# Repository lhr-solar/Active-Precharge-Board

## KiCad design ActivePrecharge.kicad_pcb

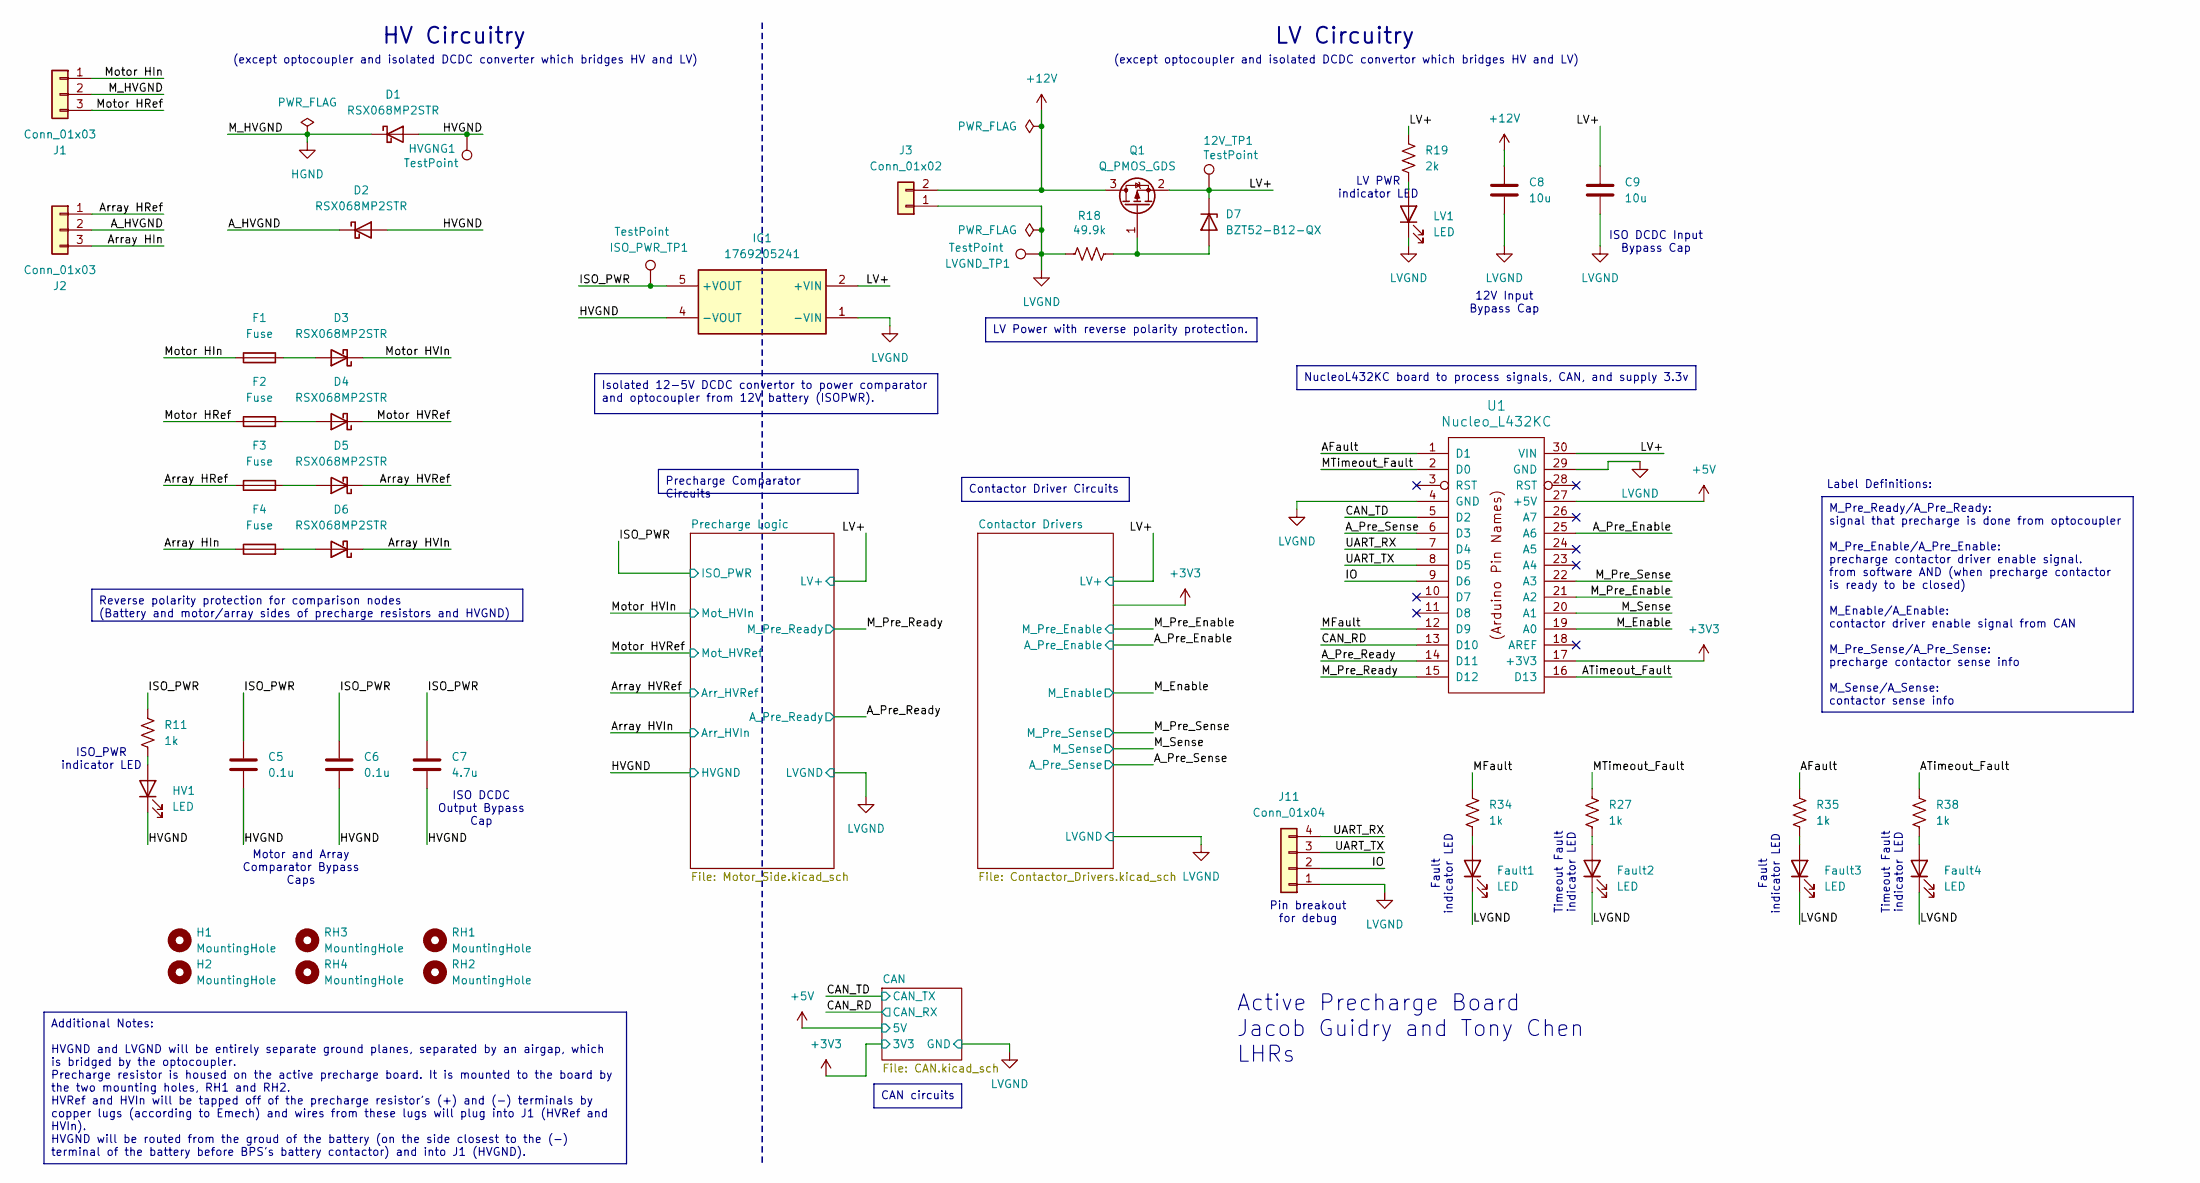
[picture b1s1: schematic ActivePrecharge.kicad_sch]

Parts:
12V_TP1: TestPoint; TestPoint_HEX_3mmID
C5, C6: 0.1u; C_0805_2012Metric
C7: 4.7u; C_0805_2012Metric
C8, C9: 10u; C_0805_2012Metric
D1, D2, D3, D4, D5, D6: RSX068MP2STR; D_SOD-123F
D7: BZT52-B12-QX; BZT52B12QX
F1, F2, F3, F4: Fuse; Fuseholder_Blade_Mini_Keystone_3568
Fault1, Fault2, Fault3, Fault4: LED; LED_0805_2012Metric
H1, H2: MountingHole; MountingHole_3mm
HV1: LED; LED_0805_2012Metric
HVGNG1: TestPoint; TestPoint_HEX_3mmID
IC1: 1769205241; Manufacturer_Part_Number 1769205241
ISO_PWR_TP1: TestPoint; TestPoint_HEX_3mmID
J1, J2: Conn_01x03; Molex_MicroFit3.0_1x3xP3.00mm_PolarizingPeg_Vertical
J3: Conn_01x02; Molex_MicroFit3.0_1x2xP3.00mm_PolarizingPeg_Vertical
J11: Conn_01x04; PinHeader_1x04_P2.54mm_Vertical
LV1: LED; LED_0805_2012Metric
LVGND_TP1: TestPoint; TestPoint_HEX_3mmID
Q1: Q_PMOS_GDS; SOT-23-3
R11, R27, R34, R35, R38: 1k; R_0805_2012Metric
R18: 49.9k; R_0805_2012Metric
R19: 2k; R_0805_2012Metric
RH1, RH2, RH3, RH4: MountingHole; MountingHole_3.2mm_M3
U1: Nucleo_L432KC; NucleoL432KC

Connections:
+3V3: U1.17 (+3V3); also elsewhere on the board
+5V: U1.27 (+5V); also elsewhere on the board
+12V: C8.1, J3.2, Q1.3 (S)
/AFault: R35.1, U1.1 (D1)
/ATimeout_Fault: R38.1, U1.16 (D13)
/A_HVGND: D2.1 (K), J2.2
/A_Pre_Enable: U1.25 (A6); also elsewhere on the board
/A_Pre_Ready: U1.14 (D11); also elsewhere on the board
/A_Pre_Sense: U1.6 (D3); also elsewhere on the board
/Array HIn: F4.1, J2.3
/Array HRef: F3.1, J2.1
/Array HVIn: D6.1 (K); also elsewhere on the board
/Array HVRef: D5.1 (K); also elsewhere on the board
/CAN_RD: U1.13 (D10); also elsewhere on the board
/CAN_TD: U1.5 (D2); also elsewhere on the board
/HVGND: C5.2, C6.2, C7.2, D1.2 (A), D2.2 (A), HV1.1 (K), HVGNG1.1, IC1.4 (-VOUT); also elsewhere on the board
/IO: J11.2, U1.9 (D6)
/ISO_PWR: C5.1, C6.1, C7.1, IC1.5 (+VOUT), ISO_PWR_TP1.1, R11.1; also elsewhere on the board
/LV+: 12V_TP1.1, C9.1, D7.1 (K), IC1.2 (+VIN), Q1.2 (D), R19.1, U1.30 (VIN); also elsewhere on the board
/MFault: R34.1, U1.12 (D9)
/MTimeout_Fault: R27.1, U1.2 (D0)
/M_Enable: U1.19 (A0); also elsewhere on the board
/M_Pre_Enable: U1.21 (A2); also elsewhere on the board
/M_Pre_Ready: U1.15 (D12); also elsewhere on the board
/M_Pre_Sense: U1.22 (A3); also elsewhere on the board
/M_Sense: U1.20 (A1); also elsewhere on the board
/Motor HIn: F1.1, J1.1
/Motor HRef: F2.1, J1.3
/Motor HVIn: D3.1 (K); also elsewhere on the board
/Motor HVRef: D4.1 (K); also elsewhere on the board
/UART_RX: J11.4, U1.7 (D4)
/UART_TX: J11.3, U1.8 (D5)
HGND: D1.1 (K), J1.2
LVGND: C8.2, C9.2, Fault1.1 (K), Fault2.1 (K), Fault3.1 (K), Fault4.1 (K), IC1.1 (-VIN), J3.1, J11.1, LV1.1 (K), LVGND_TP1.1, R18.1, U1.4 (GND), U1.29 (GND); also elsewhere on the board
unnamed: D3.2 (A), F1.2
unnamed: D4.2 (A), F2.2
unnamed: D5.2 (A), F3.2
unnamed: D6.2 (A), F4.2
unnamed: D7.2 (A), Q1.1 (G), R18.2
unnamed: Fault1.2 (A), R34.2
unnamed: Fault2.2 (A), R27.2
unnamed: Fault3.2 (A), R35.2
unnamed: Fault4.2 (A), R38.2
unnamed: HV1.2 (A), R11.2
unnamed: LV1.2 (A), R19.2

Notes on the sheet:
Precharge Comparator Circuits
M_Pre_Ready/A_Pre_Ready: signal that precharge is done from optocoupler M_Pre_Enable/A_Pre_Enable: precharge contactor driver enable signal. from software AND (when precharge contactor is ready to be closed) M_Enable/A_Enable: contactor driver enable signal from CAN M_Pre_Sense/A_Pre_Sense: prechar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
NucleoL432KC board to process signals, CAN, and supply 3.3v
LV Power with reverse polarity protection.
Contactor Driver Circuits
Additional Notes: HVGND and LVGND will be entirely separate ground planes, separated by an airgap, which is bridged by the optocoupler. Precharge resistor is housed on the active precharge board. It is mounted to the board by the two mounting holes, RH1 and RH2. HVRef and HVIn will be tapped off of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
CAN circuits
Reverse polarity protection for comparison nodes (Battery and motor/array sides of precharge resistors and HVGND)
Isolated 12-5V DCDC convertor to power comparator and optocoupler from 12V battery (ISOPWR).
LV Circuitry
ISO DCDC Input Bypass Cap
Pin breakout for debug
ISO DCDC Output Bypass Cap
HV Circuitry
Timeout Fault indicator LED
Fault indicator LED
(except optocoupler and isolated DCDC converter which bridges HV and LV)
LV PWR indicator LED
Motor and Array Comparator Bypass Caps
Label Definitions:
(except optocoupler and isolated DCDC convertor which bridges HV and LV)
12V Input Bypass Cap
ISO_PWR indicator LED
Active Precharge Board Jacob Guidry and Tony Chen LHRs

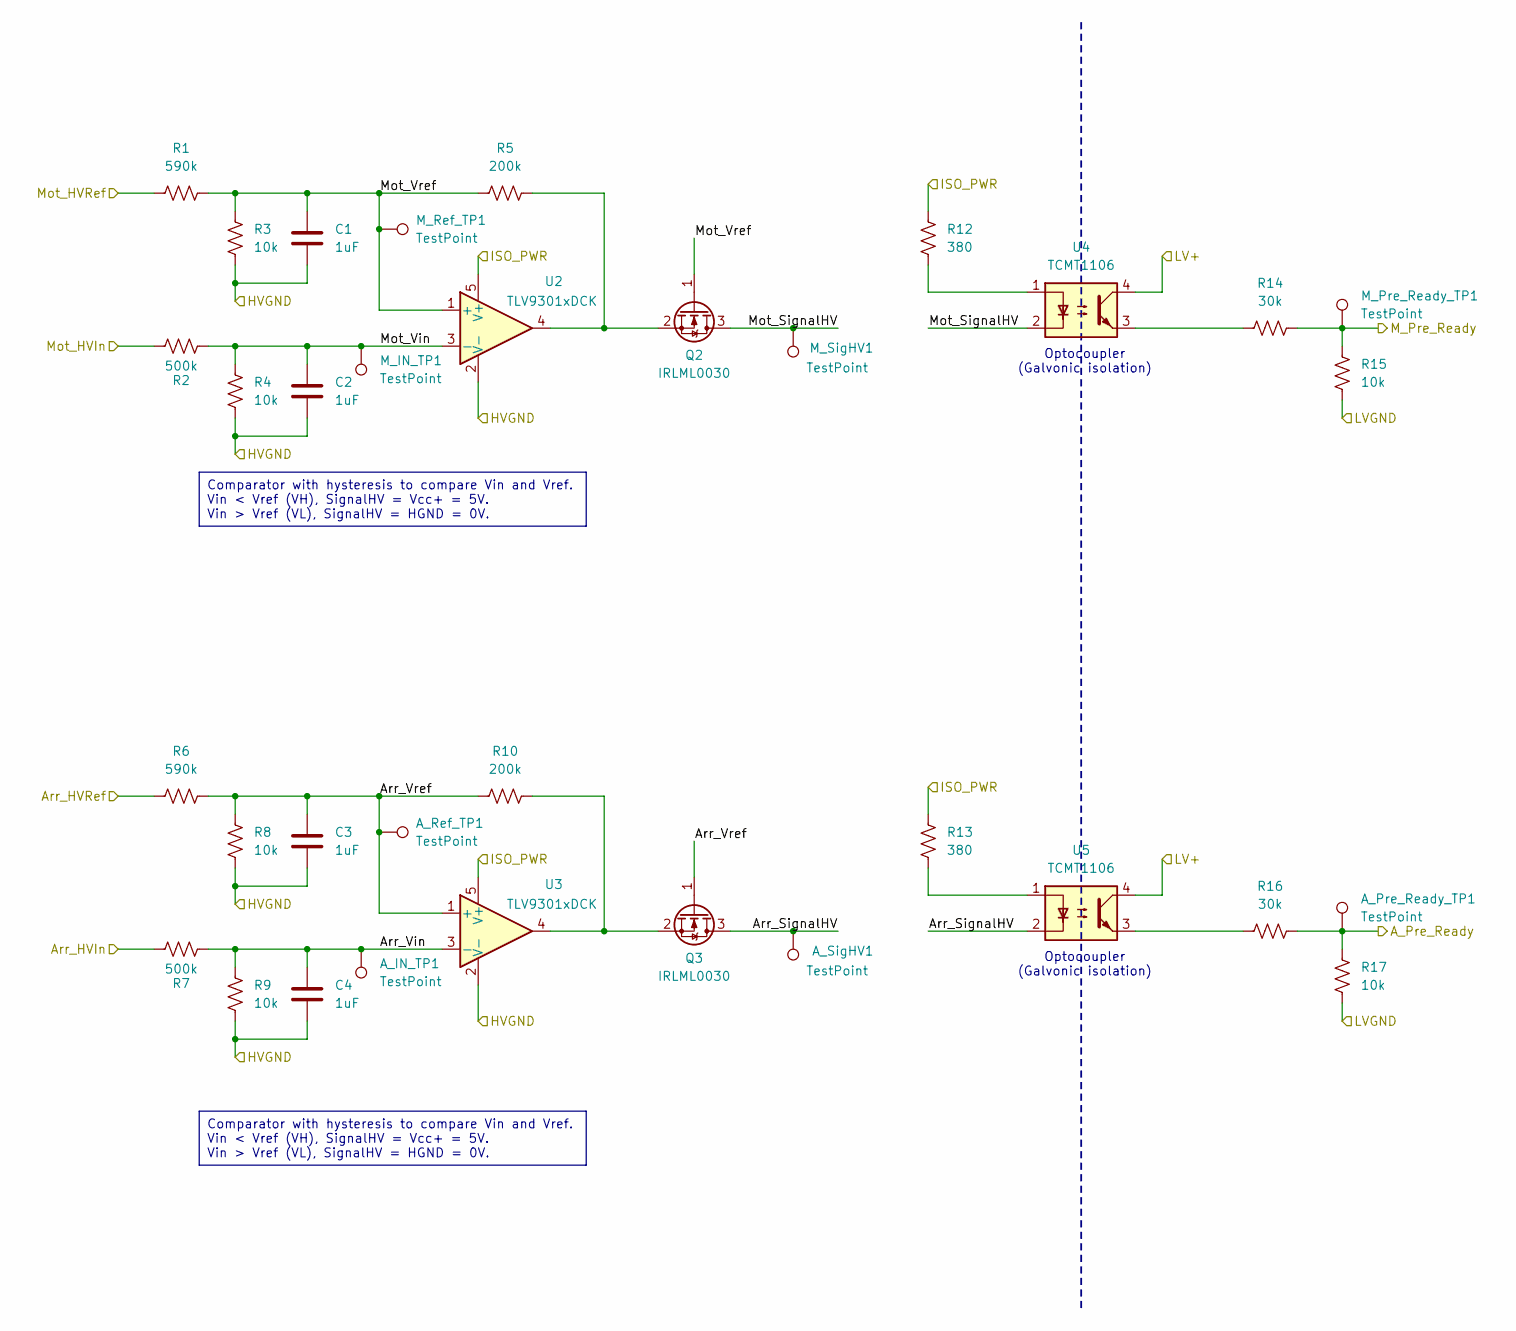
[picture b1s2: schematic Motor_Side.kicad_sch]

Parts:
A_IN_TP1: TestPoint; TestPoint_HEX_3mmID
A_Pre_Ready_TP1: TestPoint; TestPoint_HEX_3mmID
A_Ref_TP1: TestPoint; TestPoint_HEX_3mmID
A_SigHV1: TestPoint; TestPoint_HEX_3mmID
C1, C2, C3, C4: 1uF; C_0805_2012Metric
M_IN_TP1: TestPoint; TestPoint_HEX_3mmID
M_Pre_Ready_TP1: TestPoint; TestPoint_HEX_3mmID
M_Ref_TP1: TestPoint; TestPoint_HEX_3mmID
M_SigHV1: TestPoint; TestPoint_HEX_3mmID
Q2, Q3: IRLML0030; SOT-23
R1, R6: 590k; R_1206_3216Metric
R2, R7: 500k; R_1206_3216Metric
R3, R4, R8, R9, R15, R17: 10k; R_0805_2012Metric
R5, R10: 200k; R_0805_2012Metric
R12, R13: 380; R_0805_2012Metric
R14, R16: 30k; R_0805_2012Metric
U2, U3: TLV9301xDCK; SOT-353_SC-70-5
U4, U5: TCMT1106; SOP-4_4.4x2.6mm_P1.27mm

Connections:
/A_Pre_Ready: A_Pre_Ready_TP1.1, R16.2, R17.1; also elsewhere on the board
/Array HVIn: R7.2; also elsewhere on the board
/Array HVRef: R6.1; also elsewhere on the board
/HVGND: C1.2, C2.2, C3.2, C4.2, R3.2, R4.2, R8.2, R9.2, U2.2 (V-), U3.2 (V-); also elsewhere on the board
/ISO_PWR: R12.2, R13.2, U2.5 (V+), U3.5 (V+); also elsewhere on the board
/LV+: U4.4, U5.4; also elsewhere on the board
/M_Pre_Ready: M_Pre_Ready_TP1.1, R14.2, R15.1; also elsewhere on the board
/Motor HVIn: R2.2; also elsewhere on the board
/Motor HVRef: R1.1; also elsewhere on the board
/Precharge Logic/Arr_SignalHV: A_SigHV1.1, Q3.3 (D), U5.2
/Precharge Logic/Arr_Vin: A_IN_TP1.1, C4.1, R7.1, R9.1, U3.3 (-)
/Precharge Logic/Arr_Vref: A_Ref_TP1.1, C3.1, Q3.1 (G), R6.2, R8.1, R10.2, U3.1 (+)
/Precharge Logic/Mot_SignalHV: M_SigHV1.1, Q2.3 (D), U4.2
/Precharge Logic/Mot_Vin: C2.1, M_IN_TP1.1, R2.1, R4.1, U2.3 (-)
/Precharge Logic/Mot_Vref: C1.1, M_Ref_TP1.1, Q2.1 (G), R1.2, R3.1, R5.2, U2.1 (+)
LVGND: R15.2, R17.2; also elsewhere on the board
unnamed: Q2.2 (S), R5.1, U2.4
unnamed: Q3.2 (S), R10.1, U3.4
unnamed: R12.1, U4.1
unnamed: R13.1, U5.1
unnamed: R14.1, U4.3
unnamed: R16.1, U5.3

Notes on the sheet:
Comparator with hysteresis to compare Vin and Vref. Vin < Vref (VH), SignalHV = Vcc+ = 5V. Vin > Vref (VL), SignalHV = HGND = 0V.
Optocoupler (Galvonic isolation)

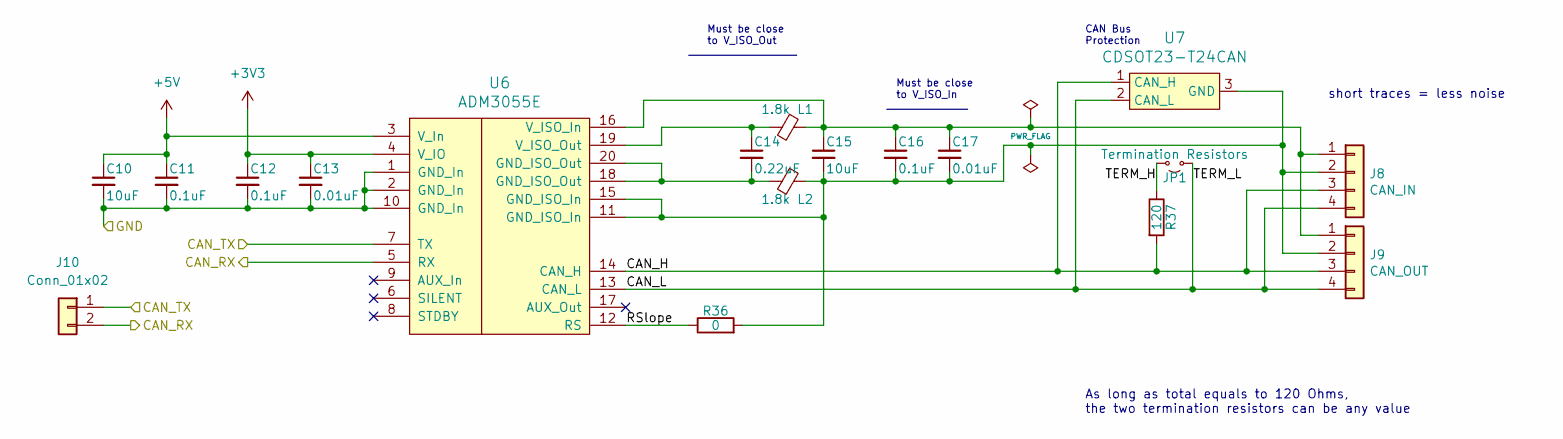
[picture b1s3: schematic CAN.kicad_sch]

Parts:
C10, C15: 10uF; C_0805_2012Metric; Mouser Part Number 963-TMK212BBJ106MGHT
C11, C12, C16: 0.1uF; C_0805_2012Metric; Mouser Part Number 80-C0805C104M5R
C13, C17: 0.01uF; C_0805_2012Metric
C14: 0.22uF; C_0805_2012Metric; Mouser Part Number 80-C0805C224J1RECTU
J8: CAN_IN; Molex_MicroFit3.0_1x4xP3.00mm_PolarizingPeg_Vertical
J9: CAN_OUT; Molex_MicroFit3.0_1x4xP3.00mm_PolarizingPeg_Vertical
J10: Conn_01x02; PinHeader_1x02_P2.54mm_Vertical
JP1: Termination Resistors; PinHeader_1x02_P2.54mm_Vertical
L1, L2: 1.8k; L_0805_2012Metric; Mouser Part Number 710-742792090
R36: 0; R_0805_2012Metric; Mouser Part Number 71-CRCW08050000Z0EAC
R37: 120; R_0805_2012Metric
U6: ADM3055E; SOIC-20W_7.5x15.4mm_Pitch1.27mm
U7: CDSOT23-T24CAN; SOT-23-3; Mouser Part Number 652-CDSOT23-T24CAN

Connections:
+3V3: C12.1, C13.1, U6.4 (V_IO); also elsewhere on the board
+5V: C10.1, C11.1, U6.3 (V_In); also elsewhere on the board
/CAN/CAN_H: J8.3, J9.3, R37.2, U6.14 (CAN_H), U7.1 (CAN_H)
/CAN/CAN_L: J8.4, J9.4, JP1.1 (A), U6.13 (CAN_L), U7.2 (CAN_L)
/CAN/RSlope: R36.1, U6.12 (RS)
/CAN/TERM_H: JP1.2 (B), R37.1
/CAN_RD: J10.2, U6.5 (RX); also elsewhere on the board
/CAN_TD: J10.1, U6.7 (TX); also elsewhere on the board
LVGND: C10.2, C11.2, C12.2, C13.2, U6.1 (GND_In), U6.2 (GND_In), U6.10 (GND_In); also elsewhere on the board
unnamed: C14.2, L2.2, U6.18 (GND_ISO_Out), U6.20 (GND_ISO_Out)
unnamed: C15.1, C16.1, C17.1, J8.1, J9.1, L1.1, U6.16 (V_ISO_In)
unnamed: C15.2, C16.2, C17.2, J8.2, J9.2, L2.1, R36.2, U6.11 (GND_ISO_In), U6.15 (GND_ISO_In), U7.3 (GND)
unnamed: C14.1, L1.2, U6.19 (V_ISO_Out)

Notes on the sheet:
Must be close to V_ISO_In
CAN Bus Protection
short traces = less noise
As long as total equals to 120 Ohms, the two termination resistors can be any value
Must be close to V_ISO_Out

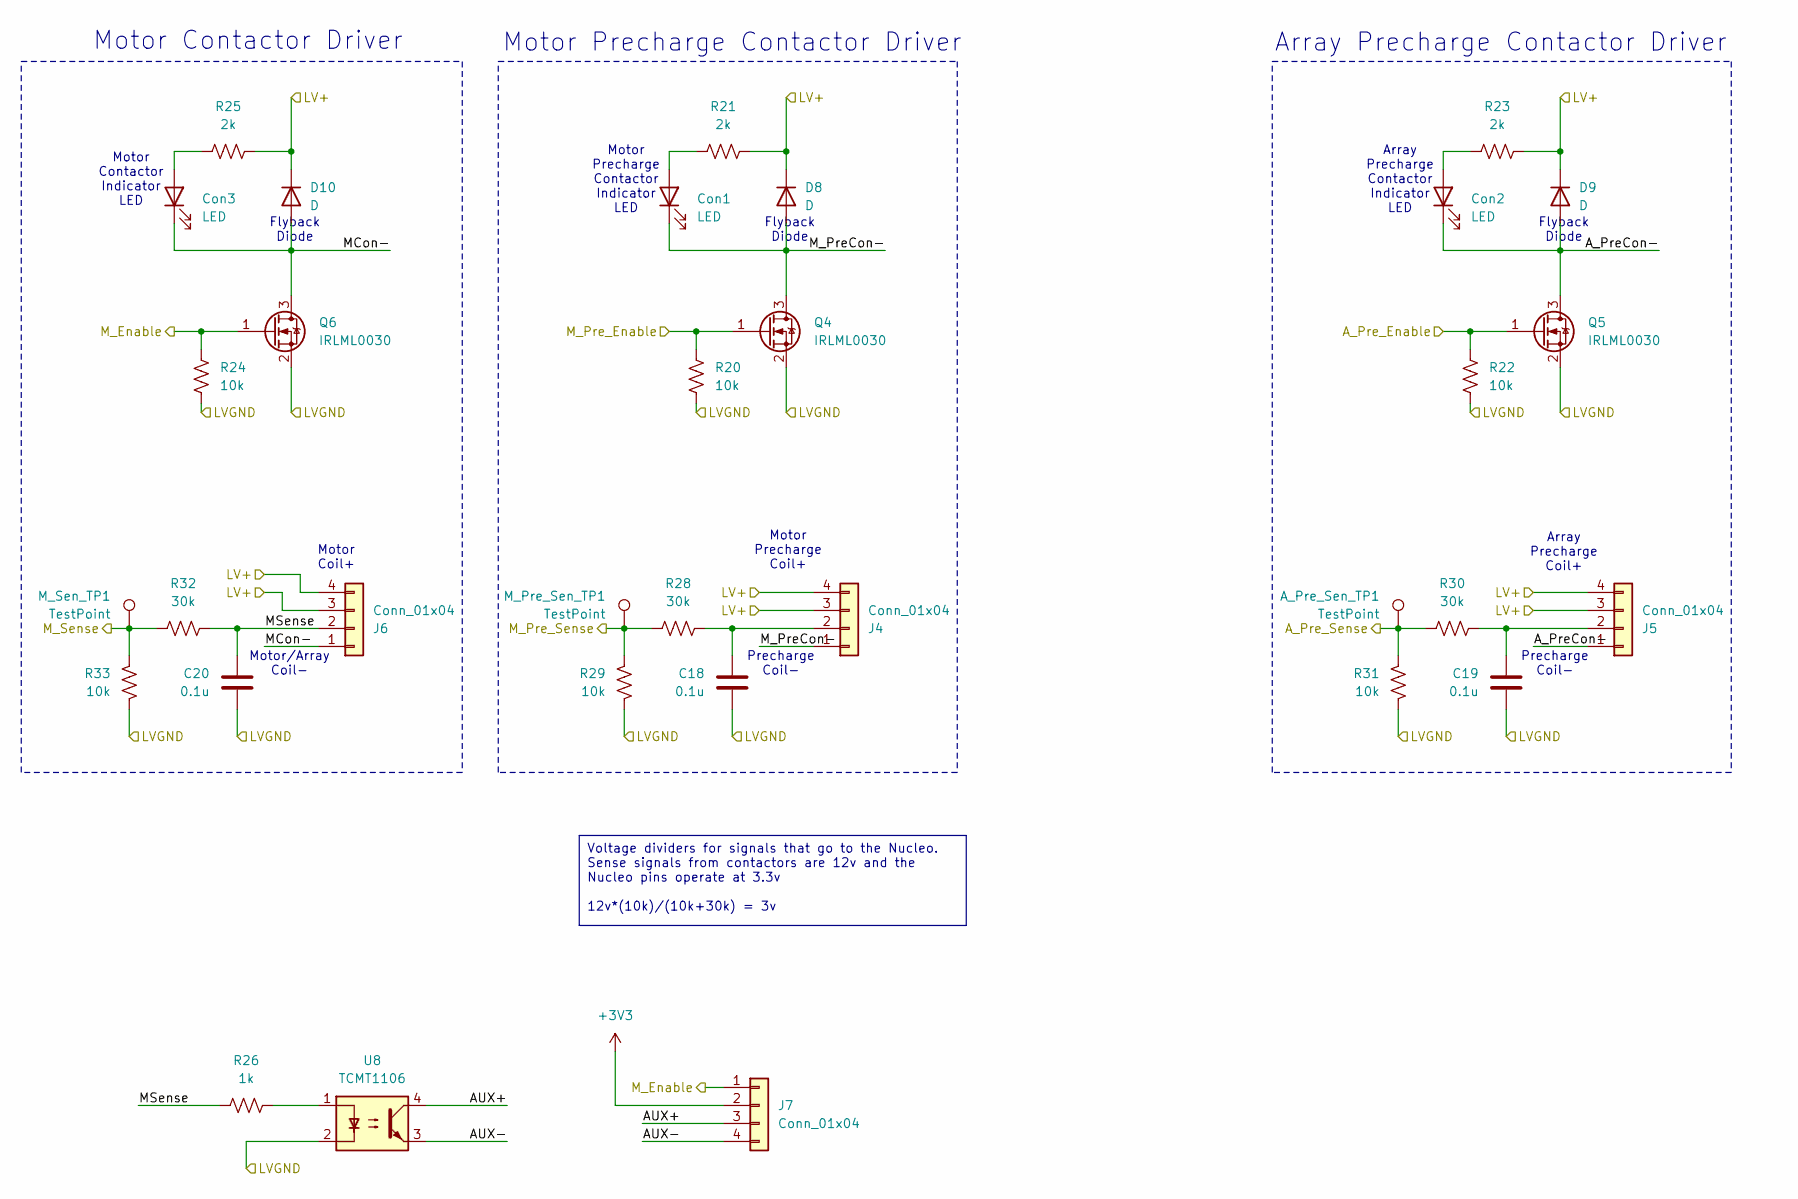
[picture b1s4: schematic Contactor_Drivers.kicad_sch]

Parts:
A_Pre_Sen_TP1: TestPoint; TestPoint_HEX_3mmID
C18, C19, C20: 0.1u; C_0805_2012Metric
Con1, Con2, Con3: LED; LED_0805_2012Metric
D8, D9, D10: D; SODFL4724X108N
J4, J5, J6, J7: Conn_01x04; Molex_MicroFit3.0_1x4xP3.00mm_PolarizingPeg_Vertical
M_Pre_Sen_TP1: TestPoint; TestPoint_HEX_3mmID
M_Sen_TP1: TestPoint; TestPoint_HEX_3mmID
Q4, Q5, Q6: IRLML0030; SOT-23
R20, R22, R24, R29, R31, R33: 10k; R_0805_2012Metric
R21, R23, R25: 2k; R_0805_2012Metric
R26: 1k; R_0805_2012Metric
R28, R30, R32: 30k; R_0805_2012Metric
U8: TCMT1106; SOP-4_4.4x2.6mm_P1.27mm

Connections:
+3V3: J7.2; also elsewhere on the board
/A_Pre_Enable: Q5.1 (G), R22.1; also elsewhere on the board
/A_Pre_Sense: A_Pre_Sen_TP1.1, R30.1, R31.1; also elsewhere on the board
/Contactor Drivers/AUX+: J7.3, U8.4
/Contactor Drivers/AUX-: J7.4, U8.3
/Contactor Drivers/A_PreCon-: Con2.1 (K), D9.2 (A), J5.1, Q5.3 (D)
/Contactor Drivers/MCon-: Con3.1 (K), D10.2 (A), J6.1, Q6.3 (D)
/Contactor Drivers/MSense: C20.1, J6.2, R26.1, R32.2
/Contactor Drivers/M_PreCon-: Con1.1 (K), D8.2 (A), J4.1, Q4.3 (D)
/LV+: D8.1 (K), D9.1 (K), D10.1 (K), J4.3, J4.4, J5.3, J5.4, J6.3, J6.4, R21.2, R23.2, R25.2; also elsewhere on the board
/M_Enable: J7.1, Q6.1 (G), R24.1; also elsewhere on the board
/M_Pre_Enable: Q4.1 (G), R20.1; also elsewhere on the board
/M_Pre_Sense: M_Pre_Sen_TP1.1, R28.1, R29.1; also elsewhere on the board
/M_Sense: M_Sen_TP1.1, R32.1, R33.1; also elsewhere on the board
LVGND: C18.2, C19.2, C20.2, Q4.2 (S), Q5.2 (S), Q6.2 (S), R20.2, R22.2, R24.2, R29.2, R31.2, R33.2, U8.2; also elsewhere on the board
unnamed: Con1.2 (A), R21.1
unnamed: Con2.2 (A), R23.1
unnamed: Con3.2 (A), R25.1
unnamed: C18.1, J4.2, R28.2
unnamed: C19.1, J5.2, R30.2
unnamed: R26.2, U8.1

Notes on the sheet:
Voltage dividers for signals that go to the Nucleo. Sense signals from contactors are 12v and the Nucleo pins operate at 3.3v 12v*(10k)/(10k+30k) = 3v
Flyback Diode
Array Precharge Contactor Driver
Precharge Coil-
Motor Contactor Indicator LED
Motor Precharge Contactor Driver
Motor Precharge Contactor Indicator LED
Motor Precharge Coil+
Array Precharge Contactor Indicator LED
Array Precharge Coil+
Motor/Array Coil-
Motor Coil+
Motor Contactor Driver

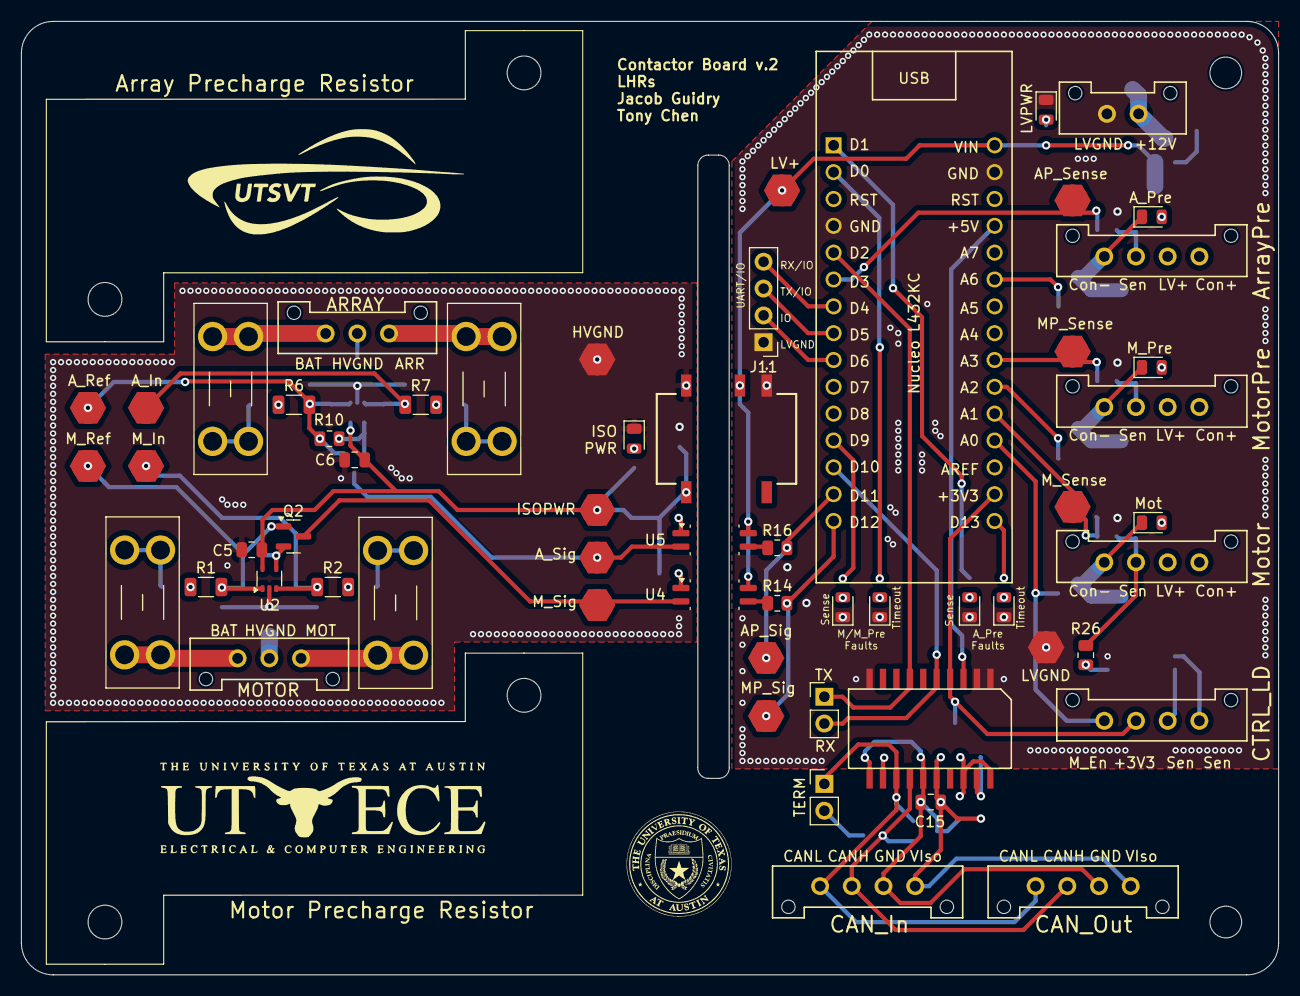
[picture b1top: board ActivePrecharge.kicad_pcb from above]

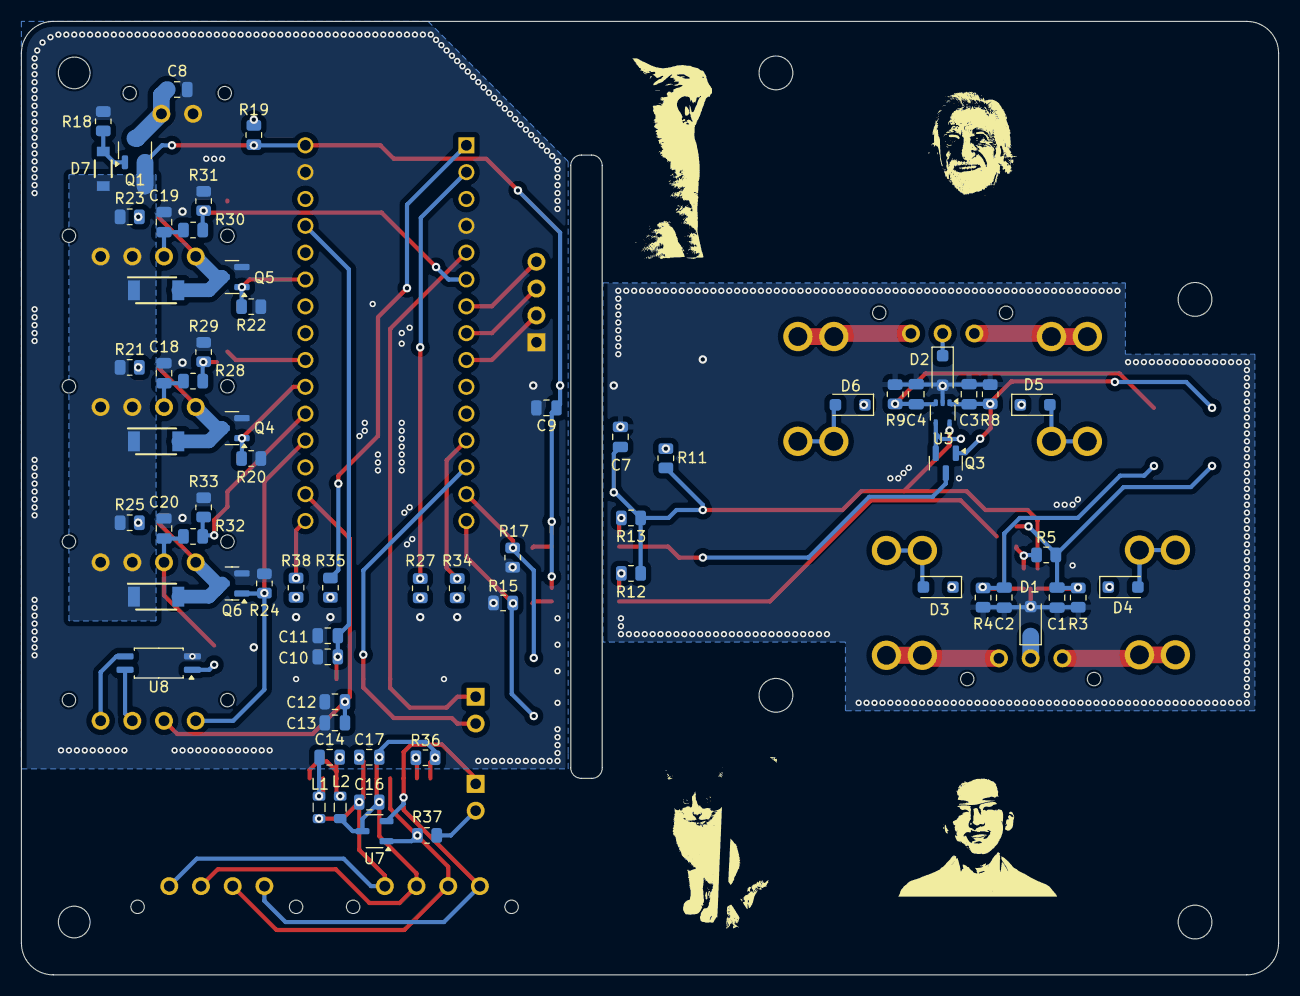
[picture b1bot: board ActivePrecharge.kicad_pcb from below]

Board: 2 copper layers, 119.0 x 90.2 mm, 131 parts (67 on the bottom side), 77 nets.

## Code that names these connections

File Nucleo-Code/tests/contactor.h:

/* USER CODE BEGIN Header */
/**
  ******************************************************************************
  * @file           : main.h
  * @brief          : Header for main.c file.
  *                   This file contains the common defines of the application.
  ******************************************************************************
  * @attention
  *
  * Copyright (c) 2025 STMicroelectronics.
  * All rights reserved.
  *
  * This software is licensed under terms that can be found in the LICENSE file
  * in the root directory of this software component.
  * If no LICENSE file comes with this software, it is provided AS-IS.
  *
  ******************************************************************************
  */
/* USER CODE END Header */

/* Define to prevent recursive inclusion -------------------------------------*/
#ifndef __MAIN_H
#define __MAIN_H

#ifdef __cplusplus
extern "C" {
#endif

/* Includes ------------------------------------------------------------------*/
#include "stm32l4xx_hal.h"
#include "CAN.h"


/* Private includes ----------------------------------------------------------*/
/* USER CODE BEGIN Includes */

/* USER CODE END Includes */

/* Exported types ------------------------------------------------------------*/
/* USER CODE BEGIN ET */

/* USER CODE END ET */

/* Exported constants --------------------------------------------------------*/
/* USER CODE BEGIN EC */

/* USER CODE END EC */

/* Exported macro ------------------------------------------------------------*/
/* USER CODE BEGIN EM */

/* USER CODE END EM */

/* Exported functions prototypes ---------------------------------------------*/
void Error_Handler(void);

/* USER CODE BEGIN EFP */

/* USER CODE END EFP */

/* Private defines -----------------------------------------------------------*/

#define blinky 1
// #define cantest 2
// #define contactorcode 3

#define m_enable_pin GPIO_PIN_0
#define mpre_enable_pin GPIO_PIN_3
#define apre_enable_pin GPIO_PIN_7
#define m_sense_pin GPIO_PIN_1
#define mpre_sense_pin GPIO_PIN_4
#define apre_sense_pin GPIO_PIN_0 // B PLEASE REMEMBER
#define mt_fault_pin GPIO_PIN_10
#define ms_fault_pin GPIO_PIN_8
#define at_fault_pin GPIO_PIN_3 // B PLEASE REMEMBER
#define as_fault_pin GPIO_PIN_9
#define mpre_ready_pin GPIO_PIN_4 // B PLEASE REMEMBER
#define apre_ready_pin GPIO_PIN_5 // B PLEASE REMEMBER

#define m_direct HAL_GPIO_ReadPin(GPIOA, m_enable_pin)

#define m_pre_enable(state) HAL_GPIO_WritePin(GPIOA, mpre_enable_pin, state)
#define a_pre_enable(state) HAL_GPIO_WritePin(GPIOA, apre_enable_pin, state)

#define m_sense HAL_GPIO_ReadPin(GPIOA, m_sense_pin)
#define m_pre_sense HAL_GPIO_ReadPin(GPIOA, mpre_sense_pin)
#define a_pre_sense HAL_GPIO_ReadPin(GPIOA, apre_sense_pin)

#define m_pre_ready HAL_GPIO_ReadPin(GPIOB, mpre_ready_pin)
#define a_pre_ready HAL_GPIO_ReadPin(GPIOB, apre_ready_pin)

#define mt_fault(state) HAL_GPIO_WritePin(GPIOA, mt_fault_pin, state)
#define ms_fault(state) HAL_GPIO_WritePin(GPIOA, ms_fault_pin, state)
#define at_fault(state) HAL_GPIO_WritePin(GPIOB, at_fault_pin, state)
#define as_fault(state) HAL_GPIO_WritePin(GPIOA, as_fault_pin, state)

 typedef enum {
    OPEN,
    CLOSED,
    FAULT
} State;

typedef enum{
  NO_FAULT,
  MT_FAULT,
  MS_FAULT,
  AT_FAULT,
  AS_FAULT
} Fault;

#define M_TIMEOUT 1000
#define MPRE_TIMEOUT 1000
#define APRE_TIMEOUT 1000

/* USER CODE BEGIN Private defines */
StaticTask_t contactortask_buffer;
StackType_t contactortask_stack[configMINIMAL_STACK_SIZE];

StaticTask_t cantask_buffer;
StackType_t cantask_stack[configMINIMAL_STACK_SIZE];

/* USER CODE END Private defines */

#ifdef __cplusplus
}
#endif

#endif /* __MAIN_H */

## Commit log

2024-10-14 ActivePreCharge-JacobGuidry-10/14/2024
2024-10-14 ActivePrecharge-JacobGuidry-10/14/2024,attempt2
2024-10-19 Jacob_AP_attepmt3
2024-10-19 add kicadlibraries
2024-10-19 Jacob ActivePrecharge footprints completed and layout started
2024-10-26 ACPR_Initial_Layout_Jacob
2024-10-26 end of workday 10/26/2024
2024-10-26 with new component footprints and cad files
2024-10-28 workday stuff
2024-10-30 sch ready for review, project specific footprint and 3d model libraries created
2024-10-31 new brannch v1
2024-10-31 selected LV bypass caps values
2024-10-31 finalized layout, fixed prechagre res dimensions
2024-11-01 removed LDO fuse, added series resistors, added to sch explinations, changed layout accordingly, sch and layout ready for review
2024-11-01 oops forgot to save last time, attempt two
2024-11-02 added silkscreen title
2024-11-02 prework day commit
2024-11-02 passes ERC now, added dimensions on layout editor
2024-11-02 fixed optocoupler data sheet link
2024-11-02 added connector labels
2024-11-02 11/2 fixed incorrect footprint and symbol
2024-11-02 HV and trace routing fixes
2024-11-02 dimension checks and silkscreen additions
2024-11-02 revert LDO HV resistor position
2024-11-02 adjusted HVGND position to be more centralized, added backplane traces and vias to route HVGND up to somewhat isolated top region, routed R1, R3 top plane traces on the back
2024-11-02 refix HVGND isolation issue
2024-11-02 fixed positioning of silkscreen labels for HV 1x3 connector
2024-11-02 fixed silkscreen and edge cuts issues
2024-11-06 initial sch and layout changes w/ test points
2024-11-06 finished layout w/ all testpoints
2024-11-06 improved tp labels, moved vias on the tp rather than next to the tp, removed ConIndVf and LVIndVf tp (pointless)
2024-11-09 Isolating Amplifiers
2024-11-10 redid sch and layout w/ reverse polarity protection on HV and LV inputs, low pass filter on comparator inputs, hystersesis on comparator
2024-11-10 buck convertor
2024-11-10 try 2
2024-11-10 updated sch explinations with new additions from today's workday
2024-11-10 fixed pmos orientation on LV reverse polarity protection, was s and d were backwards
2024-11-11 added reverse polarity protection on HV and LV inputs
2024-11-11 HV Layout w/ components on the back
2024-11-13 components places on both sides of the board for HV and LV sides, ready for review
2024-11-14 DC-DC Isolator
2024-11-16 sch done for workday 11/16/2024
2024-11-19 layout and sch ready for review (isolated DCDC convertor version)
2024-11-19 again
2024-11-19 added silkscreen labels to HV 1x3 connector
2024-11-23 small label changes
2024-11-23 changed dcdc isolator, added testpoints, added some footprints
2024-11-23 finished for review
2024-11-23 fixed incorrect pmos pinout
2024-11-25 fix isolator power labels, moved caps to reduce complexity, changed buck to 3.3v
2024-11-25 fixed adc pins
2024-12-06 pretty sch changxu approved
2024-12-08 workday schematic changes
2024-12-14 started hv layout rework w/ fuses, changed lv layout connectors
2024-12-23 schematic edits and layout prototype
2024-12-26 balancing
2024-12-26 all layout and sch changes finished, ready for frank to review
2024-12-29 pushing new changes 12/29
2024-12-31 ready for order from jlc
2024-12-31 oops didnt save
2025-01-06 v.3 ordered, fixed lv reverse polarity pmos body diode
2025-01-10 layout revisions inital draft finished
2025-01-12 added stitching vias and fixed silkscreen warnings
2025-01-15 added contactor signal connectors from v.3
2025-01-17 friday meeting for tony
2025-01-18 verify controls signals and reverse polarity schematics
2025-01-18 layout update with controls signals and fuses
2025-01-18 layout revision with controls signal, fuses, and updated schematic
2025-01-18 schematic fixes
2025-01-18 franks review: moved traces, stitching vias, Nucleo 3v3 supply
2025-01-22 stitching vias and layout changes
2025-01-23 trace routing, stitching vias, and silkscreen elements
2025-01-25 stitching vias, silkscreen elements, and trace edits
2025-01-31 contactor board first revisions
2025-02-02 workday 2/1
2025-02-02 parts sheet and cost estimate
2025-02-04 further schematic changes
2025-02-04 fixed some ERC errors, incorrect connectors
2025-02-04 signals text box
2025-02-05 started on HV layout
2025-02-06 changed labels
2025-02-07 fixed lakshay and ravi comments, renamed signals to be more readable, further worked on HV side layout
2025-02-07 forgot to save, try again
2025-02-08 end of workday, will work on more tonight
2025-02-09 layout nearly finalized for review
2025-02-10 layout finalized and ready for review
2025-02-10 changed last label, ready for review
2025-02-11 adjusted based off ravi and frank
2025-02-12 layout review fixes
2025-02-15 added debounce caps to sense pins of contactors
2025-02-16 embedded sharepoint
2025-02-22 removed embedded sharepoint
2025-02-22 tony yelled at me
2025-02-22 Revert "ah"
    This reverts commit 69442e2ad7ee22fee0c7b27c042d5ebbb3afea37.
2025-02-22 Revert "removed embedded sharepoint"
    This reverts commit a8307f65af0d5a4552b66320072bf494f017b56f.
2025-02-22 no head bang
2025-02-22 rm gerbers again
2025-02-22 rm gerbers
2025-02-23 add logic diagram
2025-03-01 pre workday stuff
2025-03-03 workday pain
2025-03-06 initial commit v2
2025-03-07 fixed HV layout and added the both nmos
2025-03-10 oops forgot to push workday changes 3/8/25
2025-03-16 contactor code
2025-03-17 layout finalized just need to make labels prettier
2025-03-17 layout finalized for review
2025-03-18 fixed can signal traces
2025-03-18 ready for final review and order
2025-03-19 ready to order
2025-03-19 ok ready again
2025-03-21 changed some res values
2025-03-24 changed more resistor values on SCH
2025-03-27 makefile
2025-03-29 makefile fr this time
2025-03-29 fix small issue hehe
2025-04-01 contactor can task
2025-04-02 fixing submodule bs
2025-04-02 bump sharepoint + gitignore
2025-04-02 init task
2025-04-03 started restructuring
2025-04-11 timeout and sense fault
2025-04-12 nucleo code
2025-04-12 4/12/25 workday
2025-04-14 can workie
2025-04-14 balls
2025-04-16 new revision for frank review
2025-04-17 emergency m_enable fix
2025-04-26 code stuff
2025-05-01 motor logic tested and fully functional 4/29/2025, need to test array
2025-05-01 fixed multiple definitions error, still using old logic
2025-05-02 start combining restructure, make pin defs more readable
2025-05-02 add function defs to header
2025-05-02 fully restructure files to match other branch
2025-05-02 fix functions to use new macros
2025-05-02 code compiles again
2025-05-03 move contactor functionality to driver so i can make a test
2025-05-03 start adding tesst
2025-05-03 status LED driver + tests
2025-05-03 static
2025-05-03 remove all old status stuff
2025-05-03 contactor task test
2025-05-04 make faults distinct
2025-05-06 fix contactor state>
2025-05-07 time to nuke this
2025-05-07 file structure, CAN/statusLED drivers, init task, tests
2025-05-08 start contactors driver, CAN metadata
2025-05-08 new enum, struct, function headers
2025-05-08 setContactor
2025-05-09 contactors init/get
2025-05-09 contactors_set and precharge fault handling
2025-05-09 dumb
2025-05-11 lakslay
2025-05-11 blah blah
2025-05-11 more faults
2025-05-11 ign state
2025-05-11 fawlt
2025-05-11 BPS/controls safety status
2025-05-11 get hv+/-
2025-05-13 cigol
2025-05-13 add precharge/sense timers
2025-05-14 tests for timer/getprecharge
2025-05-14 beep boop
2025-05-14 can no work
2025-05-14 pls help me lakshay.
2025-05-16 ignition bitmap
2025-05-16 sense fault handler
2025-05-16 stuff
2025-05-16 poopie stinky doo doo
2025-05-16 crashout
2025-05-18 timers 🖕
2025-05-18 boom
2025-05-19 send fault repeatedly
2025-05-19 can't
2025-05-20 modified config vals (still no work)
2025-05-20 WORKING CAN CONFIG TESTED ON HARDWARE FUCK YALL HATERS ONG IM GONNA CRASHOUT
2025-05-20 fix can init in main
2025-05-25 made io_state queue smaller
2025-05-25 testing motor ignition
2025-05-25 poop
2025-05-25 workie
2025-05-25 workie but w/ leds
2025-05-25 temporarily removed array precharge to test motor
2025-05-26 working
2025-06-07 stugg
2025-06-07 workie again
2025-06-08 ravi shah
2025-06-27 changed data length
2025-07-04 added support for ending precharge before completion
2025-08-15 MVP contactor board firmware (#9)
    * delete useless files
    * file structure, CAN/statusLED drivers, init task, tests
    * start contactors driver, CAN metadata
    * new enum, struct, function headers
    * setContactor
    * contactors init/get
